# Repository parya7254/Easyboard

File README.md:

# Easyboard
A hot swappable tenkeyless (full size but without the number pad) mechanical keyboard with RGB lighting and an OLED (SSD1306) display! It will use a RP2040 Pro Micro as the controller, SK6812-MINI-E (reverse mount) LEDs for the backlight, and MX-style switches (and also MX-style hot swap sockets).

# Why did I Make This??
I really like designing my own things, like REALLY. And I also REALLY want a mechanical keyboard. So I thought to myself, *why not just make your own?* So I did one of my most complex projects ever, designing and building my own hot-swappable keyboard with RGB lights. And after about *more than* 60 **MIND GRUELING** hours of work, I managed to finally make a mechanical keyboard, one that was made by **me** and **me** only. And another reason for making this keyboard is that I have a lot of school work which requires a lot of typing and sometimes I write a lot of code, so this keyboard will help me work more efficiently.

# How did I Make This??
All of the PCB designing was done in KiCad and the case was designed in Fusion360. I started with a scematic and layed out my parts like so: 

And after that, I placed my parts on the PCB and then wired them:

The hardest part of designing this keyboard was wiring the things together in my PCB, expecially the LEDs. I ran into many rabbit holes during this process since lots of things were in the way and there was not encough space to wire some things so I had to move some traces and sometimes entirely rewire some things just so I can wire other things. Designing the keyboard made me want to give up and scrap everything and start another project, but I still continued and managed to finish everything.

# BOM
These are the parts that I need to build and assemble my PCB:

| Name | Purpose | Quantity | Total Cost (USD) | Link | Distributor |
|---|---|---|---|---|---|
| SSD1306 OLED Display | This will be the display on my keyboard. I currently plan on having it display the mode of the right 9 extra switches. | 1 | 2.50 | https://www.aliexpress.us/item/3256805954920554.html?spm=a2g0o.productlist.main.1.acdaE2guE2guy6&algo_pvid=447a40fe-ce76-4550-b662-5327f82a75f7&algo_exp_id=447a40fe-ce76-4550-b662-5327f82a75f7-0&pdp_ext_f=%7B%22order%22%3A%2222914%22%2C%22eval%22%3A%221%22%2C%22fromPage%22%3A%22search%22%7D&pdp_npi=6%40dis%21USD%212.51%212.50%21%21%2117.24%2117.15%21%402101f70717749984566174141ee445%2112000035944225408%21sea%21US%21861143113%21X%211%210%21n_tag%3A-29919%3Bd%3A19af3db4%3Bm03_new_user%3A-29895&curPageLogUid=5KU5UVX5hVAo&utparam-url=scene%3Asearch%7Cquery_from%3A%7Cx_object_id%3A1005006141235306%7C_p_origin_prod%3A | AliExpress |
| MX Stabilizers | These will be the stabilizers for the longer keys on my keyboard. This will ensure that the longer keycaps properly press when not pressed from the middle. | 1 | 2.86 | https://www.aliexpress.us/item/3256807026554334.html?spm=a2g0o.productlist.main.1.698f24e6GPCOAO&algo_pvid=6986125a-1875-4abe-a369-b66edb9fdb96&algo_exp_id=6986125a-1875-4abe-a369-b66edb9fdb96-0&pdp_ext_f=%7B%22order%22%3A%2283%22%2C%22eval%22%3A%221%22%2C%22fromPage%22%3A%22search%22%7D&pdp_npi=6%40dis%21USD%212.86%212.86%21%21%2119.65%2119.65%21%402101e2b017749981124183121e3966%2112000039826435204%21sea%21US%21861143113%21X%211%210%21n_tag%3A-29919%3Bd%3A19af3db4%3Bm03_new_user%3A-29895&curPageLogUid=vXwvaFnDovX6&utparam-url=scene%3Asearch%7Cquery_from%3A%7Cx_object_id%3A1005007212869086%7C_p_origin_prod%3A | AliExpress |
| Blue MX Hotswap Sockets (110pcs) | This will be to sockets which I solder to the PCB and where I insert my keyboard's switches. | 1 | 12.99 | https://www.amazon.com/DUROCK-Mechanical-Keyboard-Switches-Hot-Swap/dp/B0B4W8WFGS/ref=sr_1_7?crid=3PNPV81A8PUH7&dib=eyJ2IjoiMSJ9.JKoXkJJJrIVA4JnSSkGnSnjGCC1c4hQes6g1zrF8pFvOIEmMfUgJ5pp02OFyf2JeWhCTJmnAN4q3G-LvLOuBql6VJTJnxRGewD6-XjfYxSGo6HtCUGx8yAxFKqo13-YgVgIDzEERzdctNqCARGlgTNMMWP0Cxdv0wlmfE63BKVlXHsFmkzjJEkMkOGy9lDu44t9_Vt13ecWd9WDIXfqE_Q.RRCHw5LNrbPmqY88z8aOQsue-Tfpf6xlrtRnIY_J_gQ&dib_tag=se&keywords=hotswap%2Bsockets%2Bmx&qid=1774997653&sprefix=hotswap%2Bsocket%2Caps%2C140&sr=8-7&th=1 | Amazon |
| Keyboard PCB | This will be the main part of my keyboard! This is my circuit board with connects the components to the RP2040 Pro Micro. | 5 | 27.00 | https://cart.jlcpcb.com/quote?spm=jlcpcb.Public.2006 | JLCPCB |
| Green Frosted Translucent Clear Keycaps Set | These will be the keycaps for my keyboard! I chose the color green and also they are transparent so that the RGB lights shine though. | 1 | 16.99 | https://www.amazon.com/GUUKEY-Translucent-Shine-Through-Transparency-Mechanical/dp/B0FLK96YHS/ref=sr_1_3?crid=1ENZ1X3ES00VQ&dib=eyJ2IjoiMSJ9.I7pnMYchsMp-bVFs-8t_5AumUR2fDrr8YE76gmEcZGbXdxlwJu8_AAkgVcEPEsNVSN_SA7HxV4aJbe8cyMGeu89ntH00LOWfRLWGlidNYcLFfGzSm5UkZHD4eGqyAo5XHeqoyGSxBD-OXpWZBtiG16iisgaG0eoEzXPDPi6twUEGshXSF9cS__vJKIL8_iDx0pKE8X016OgZCxUxqKfG2d8N3Dy_bG0HyyhEg2jRx-Q.m5fVCbWabIUWUqADZR7fq_V4eNC2APTzMw1I3X1rxQQ&dib_tag=se&keywords=transparent%2Bgreen%2Bkeycaps%2Bmx&qid=1774990147&sprefix=transparent%2Bgreen%2Bkeycaps%2Bmx%2Caps%2C133&sr=8-3&th=1 | Amazon |
| SK6812 MINI-E (100pcs) | This will be the RGB LEDs of my keyboard! They are individually addressable as well (each led can have its own color) and they will add great aesthetics to my keyboard. | 1 | 3.49 | https://www.aliexpress.us/item/3256807677321116.html?spm=a2g0o.productlist.main.2.35d357e6bXG6Fa&algo_pvid=9bae5c18-19c7-4431-a748-378d3deebd81&algo_exp_id=9bae5c18-19c7-4431-a748-378d3deebd81-1&pdp_ext_f=%7B%22order%22%3A%22531%22%2C%22eval%22%3A%221%22%2C%22fromPage%22%3A%22search%22%7D&pdp_npi=6%40dis%21USD%213.49%213.49%21%21%213.49%213.49%21%402101d6fe17749205864375340ec439%2112000042594617264%21sea%21US%21861143113%21X%211%210%21n_tag%3A-29919%3Bd%3A19af3db4%3Bm03_new_user%3A-29895&curPageLogUid=H9eLn4OdO0JY&utparam-url=scene%3Asearch%7Cquery_from%3A%7Cx_object_id%3A1005007863635868%7C_p_origin_prod%3A | AliExpress |
| RP2040 Pro Micro | This is my keyboard's microcontroller. It will read the key presses from the key matrix and then convert them into key presses and then send keyboard commands to the connected device and it also will control the RGB lighting and the OLED display.. It is basically the ""brain"" of my keyboard. | 1 | 3.82 | https://www.aliexpress.us/item/3256806781060135.html?spm=a2g0o.productlist.main.1.75d062b2eSWZgQ&algo_pvid=1db491c0-3181-4dad-b148-b2b95c9bb695&algo_exp_id=1db491c0-3181-4dad-b148-b2b95c9bb695-0&pdp_ext_f=%7B%22order%22%3A%227169%22%2C%22eval%22%3A%221%22%2C%22orig_sl_item_id%22%3A%221005006967374887%22%2C%22orig_item_id%22%3A%221005009890367599%22%2C%22fromPage%22%3A%22search%22%7D&pdp_npi=6%40dis%21USD%216.48%213.11%21%21%2144.66%2121.44%21%402101df0e17749198865717046e5ea2%2112000038886039687%21sea%21US%21861143113%21XZ%211%210%21n_tag%3A-29919%3Bd%3A19af3db4%3Bm03_new_user%3A-29895&curPageLogUid=SrAHQR9XW5yz&utparam-url=scene%3Asearch%7Cquery_from%3A%7Cx_object_id%3A1005006967374887%7C_p_origin_prod%3A1005009890367599 | AliExpress |
| EPOMAKER Shadow Black Switches (100pcs) | These are the switches which will be used for my keyboard! | 1 | 19.99 | https://www.amazon.com/EPOMAKER-Mechanical-Switches-Keyboard-Pre-Lubed/dp/B0FYDQZ8HB/ref=sr_1_11?crid=1U34LH1S6O4TT&dib=eyJ2IjoiMSJ9.sZD0w0fIzMUCaV5YG3puFGZtG6dwW4pUS_EZhR3f8hiDH3pp0GB4T2VaDawQc9IybRuM4PJDiF0WhQhyN6jvBzeUSHCTjH3YTej49KHc8NuGcii3WUYmKEu9XZ83Us3_Xm0L7yCCNyTN1sGkM6aCd1uegF4RXI-MPjx5nbcpCevXdNGoZcz4q2Wl7Gohq1Nfs3aY56FeV-rw70tCRazUEOPahTbWXUitNsm_dx2fmo4.vV0_W4ZE6EAypwP-uPtM1gzeZPcmb4dmKXFzgEeno0A&dib_tag=se&keywords=100%2Bkeyboard%2Bswitch&qid=1775004672&sprefix=100%2Bkeyboard%2Bswitch%2Caps%2C169&sr=8-11&th=1 | Amazon |

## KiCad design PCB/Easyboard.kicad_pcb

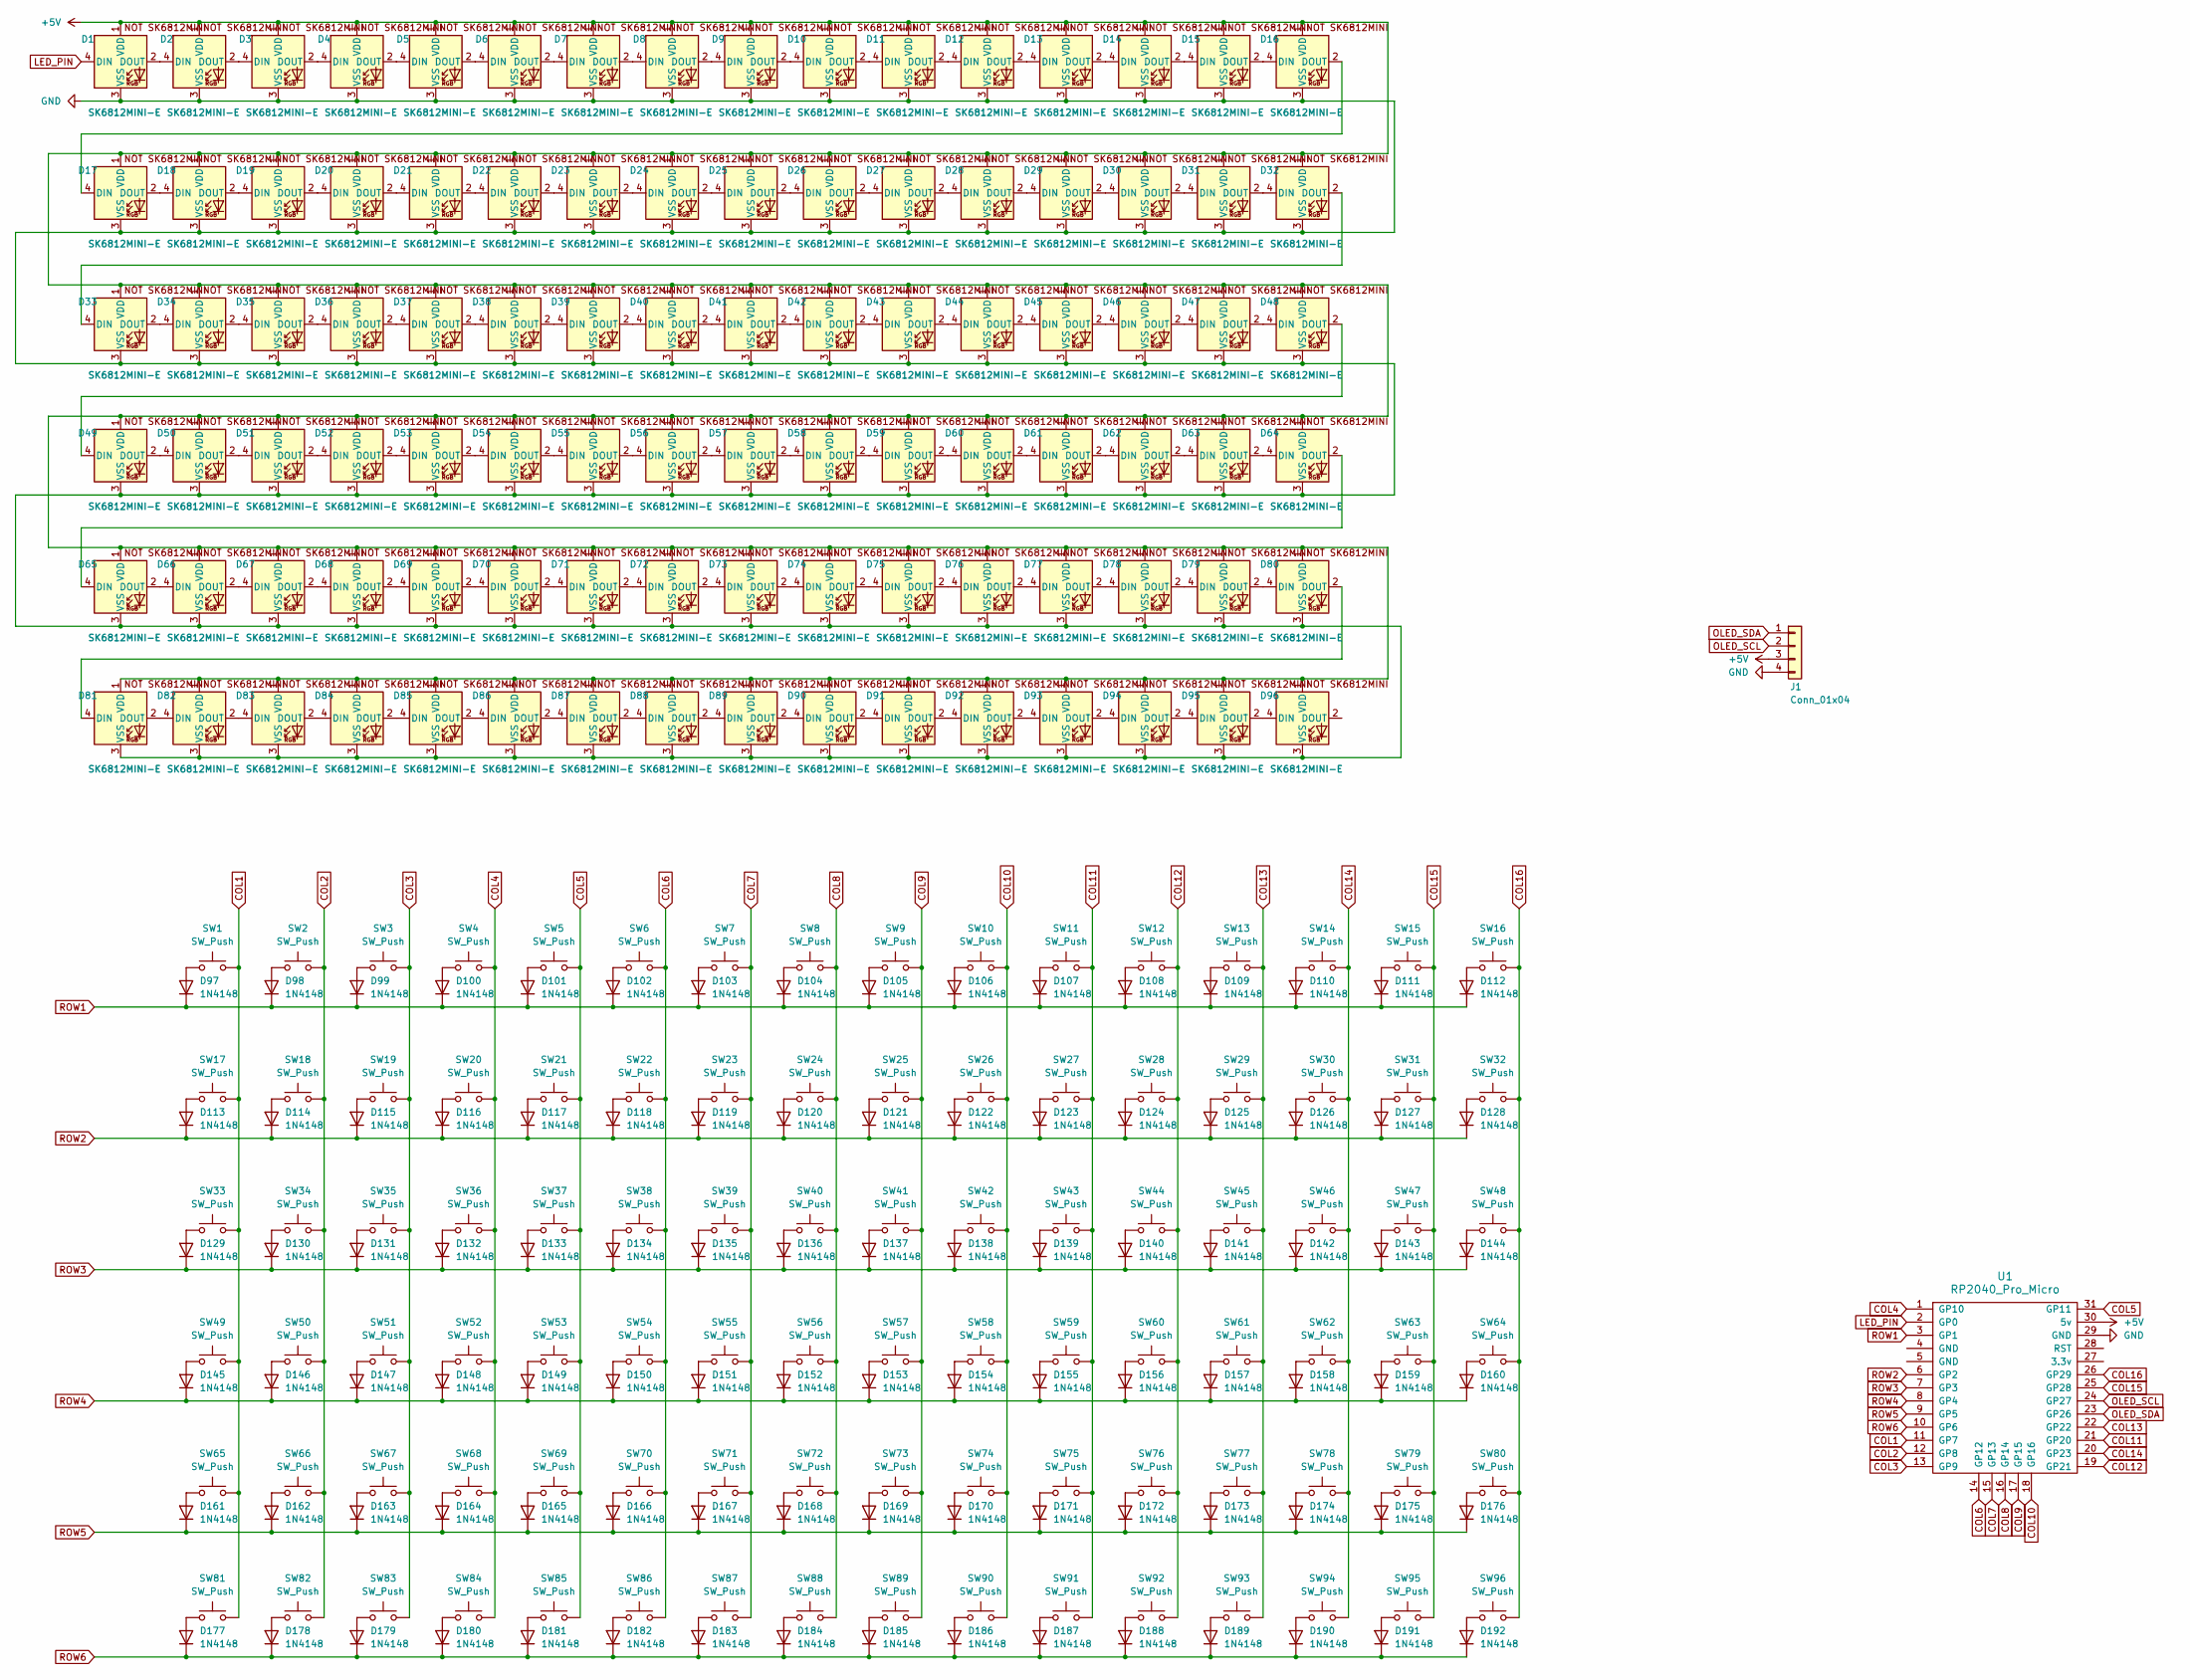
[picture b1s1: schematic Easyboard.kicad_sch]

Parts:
D1, D2, D3, D4, D5, D6, D7, D8, D9, D10, D11, D12, D13, D14, D15, D16, D17, D18, D19, D20, D21, D22, D23, D24, D25, D26, D27, D28, D29, D30, D31, D32, D33, D34, D35, D36, D37, D38, D39, D40, D41, D42, D43, D44, D45, D46, D47, D48, D49, D50, D51, D52, D53, D54, D55, D56, D57, D58, D59, D60, D61, D62, D63, D64, D65, D66, D67, D68, D69, D70, D71, D72, D73, D74, D75, D76, D77, D78, D79, D80, D81, D82, D83, D84, D85, D86, D87, D88, D89, D90, D91, D92, D93, D94, D95, D96: SK6812MINI-E; MX_SK6812MINI-E_REV
D97, D98, D99, D100, D101, D102, D103, D104, D105, D106, D107, D108, D109, D110, D111, D112, D113, D114, D115, D116, D117, D118, D119, D120, D121, D122, D123, D124, D125, D126, D127, D128, D129, D130, D131, D132, D133, D134, D135, D136, D137, D138, D139, D140, D141, D142, D143, D144, D145, D146, D147, D148, D149, D150, D151, D152, D153, D154, D155, D156, D157, D158, D159, D160, D161, D162, D163, D164, D165, D166, D167, D168, D169, D170, D171, D172, D173, D174, D175, D176, D177, D178, D179, D180, D181, D182, D183, D184, D185, D186, D187, D188, D189, D190, D191, D192: 1N4148; D_DO-35_SOD27_P7.62mm_Horizontal
J1: Conn_01x04; PinHeader_1x04_P2.54mm_Vertical
SW1, SW2, SW3, SW4, SW5, SW6, SW7, SW8, SW9, SW10, SW11, SW12, SW13, SW14, SW15, SW16, SW17, SW18, SW19, SW20, SW21, SW22, SW23, SW24, SW25, SW26, SW27, SW28, SW29, SW31, SW32, SW33, SW35, SW36, SW37, SW38, SW39, SW40, SW41, SW42, SW43, SW44, SW45, SW46, SW48, SW49, SW50, SW52, SW53, SW54, SW55, SW56, SW57, SW58, SW59, SW60, SW61, SW62, SW65, SW66, SW67, SW68, SW69, SW70, SW71, SW72, SW73, SW74, SW76, SW85, SW86, SW87, SW88, SW89, SW90, SW91, SW92, SW93, SW94, SW95, SW96: SW_Push; Hotswap_MX_1.00u
SW30: SW_Push; Hotswap_MX_2.00u
SW34, SW47: SW_Push; Hotswap_MX_1.50u
SW51: SW_Push; Hotswap_MX_1.75u
SW63, SW64: SW_Push; Hotswap_MX_2.25u
SW75: SW_Push; Hotswap_MX_2.75u
SW77, SW78, SW79, SW81, SW82, SW83, SW84: SW_Push; Hotswap_MX_1.25u
SW80: SW_Push; Hotswap_MX_6.25u
U1: RP2040_Pro_Micro

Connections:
+5V: D1.1 (VDD), D2.1 (VDD), D3.1 (VDD), D4.1 (VDD), D5.1 (VDD), D6.1 (VDD), D7.1 (VDD), D8.1 (VDD), D9.1 (VDD), D10.1 (VDD), D11.1 (VDD), D12.1 (VDD), D13.1 (VDD), D14.1 (VDD), D15.1 (VDD), D16.1 (VDD), D17.1 (VDD), D18.1 (VDD), D19.1 (VDD), D20.1 (VDD), D21.1 (VDD), D22.1 (VDD), D23.1 (VDD), D24.1 (VDD), D25.1 (VDD), D26.1 (VDD), D27.1 (VDD), D28.1 (VDD), D29.1 (VDD), D30.1 (VDD), D31.1 (VDD), D32.1 (VDD), D33.1 (VDD), D34.1 (VDD), D35.1 (VDD), D36.1 (VDD), D37.1 (VDD), D38.1 (VDD), D39.1 (VDD), D40.1 (VDD), D41.1 (VDD), D42.1 (VDD), D43.1 (VDD), D44.1 (VDD), D45.1 (VDD), D46.1 (VDD), D47.1 (VDD), D48.1 (VDD), D49.1 (VDD), D50.1 (VDD), D51.1 (VDD), D52.1 (VDD), D53.1 (VDD), D54.1 (VDD), D55.1 (VDD), D56.1 (VDD), D57.1 (VDD), D58.1 (VDD), D59.1 (VDD), D60.1 (VDD), D61.1 (VDD), D62.1 (VDD), D63.1 (VDD), D64.1 (VDD), D65.1 (VDD), D66.1 (VDD), D67.1 (VDD), D68.1 (VDD), D69.1 (VDD), D70.1 (VDD), D71.1 (VDD), D72.1 (VDD), D73.1 (VDD), D74.1 (VDD), D75.1 (VDD), D76.1 (VDD), D77.1 (VDD), D78.1 (VDD), D79.1 (VDD), D80.1 (VDD), D81.1 (VDD), D82.1 (VDD), D83.1 (VDD), D84.1 (VDD), D85.1 (VDD), D86.1 (VDD), D87.1 (VDD), D88.1 (VDD), D89.1 (VDD), D90.1 (VDD), D91.1 (VDD), D92.1 (VDD), D93.1 (VDD), D94.1 (VDD), D95.1 (VDD), D96.1 (VDD), J1.3, U1.30 (5v)
COL1: SW1.2, SW17.2, SW33.2, SW49.2, SW65.2, SW81.2, U1.11 (GP7)
COL2: SW2.2, SW18.2, SW34.2, SW50.2, SW66.2, SW82.2, U1.12 (GP8)
COL3: SW3.2, SW19.2, SW35.2, SW51.2, SW67.2, SW83.2, U1.13 (GP9)
COL4: SW4.2, SW20.2, SW36.2, SW52.2, SW68.2, SW84.2, U1.1 (GP10)
COL5: SW5.2, SW21.2, SW37.2, SW53.2, SW69.2, SW85.2, U1.31 (GP11)
COL6: SW6.2, SW22.2, SW38.2, SW54.2, SW70.2, SW86.2, U1.14 (GP12)
COL7: SW7.2, SW23.2, SW39.2, SW55.2, SW71.2, SW87.2, U1.15 (GP13)
COL8: SW8.2, SW24.2, SW40.2, SW56.2, SW72.2, SW88.2, U1.16 (GP14)
COL9: SW9.2, SW25.2, SW41.2, SW57.2, SW73.2, SW89.2, U1.17 (GP15)
COL10: SW10.2, SW26.2, SW42.2, SW58.2, SW74.2, SW90.2, U1.18 (GP16)
COL11: SW11.2, SW27.2, SW43.2, SW59.2, SW75.2, SW91.2, U1.21 (GP20)
COL12: SW12.2, SW28.2, SW44.2, SW60.2, SW76.2, SW92.2, U1.19 (GP21)
COL13: SW13.2, SW29.2, SW45.2, SW61.2, SW77.2, SW93.2, U1.22 (GP22)
COL14: SW14.2, SW30.2, SW46.2, SW62.2, SW78.2, SW94.2, U1.20 (GP23)
COL15: SW15.2, SW31.2, SW47.2, SW63.2, SW79.2, SW95.2, U1.25 (GP28)
COL16: SW16.2, SW32.2, SW48.2, SW64.2, SW80.2, SW96.2, U1.26 (GP29)
GND: D1.3 (VSS), D2.3 (VSS), D3.3 (VSS), D4.3 (VSS), D5.3 (VSS), D6.3 (VSS), D7.3 (VSS), D8.3 (VSS), D9.3 (VSS), D10.3 (VSS), D11.3 (VSS), D12.3 (VSS), D13.3 (VSS), D14.3 (VSS), D15.3 (VSS), D16.3 (VSS), D17.3 (VSS), D18.3 (VSS), D19.3 (VSS), D20.3 (VSS), D21.3 (VSS), D22.3 (VSS), D23.3 (VSS), D24.3 (VSS), D25.3 (VSS), D26.3 (VSS), D27.3 (VSS), D28.3 (VSS), D29.3 (VSS), D30.3 (VSS), D31.3 (VSS), D32.3 (VSS), D33.3 (VSS), D34.3 (VSS), D35.3 (VSS), D36.3 (VSS), D37.3 (VSS), D38.3 (VSS), D39.3 (VSS), D40.3 (VSS), D41.3 (VSS), D42.3 (VSS), D43.3 (VSS), D44.3 (VSS), D45.3 (VSS), D46.3 (VSS), D47.3 (VSS), D48.3 (VSS), D49.3 (VSS), D50.3 (VSS), D51.3 (VSS), D52.3 (VSS), D53.3 (VSS), D54.3 (VSS), D55.3 (VSS), D56.3 (VSS), D57.3 (VSS), D58.3 (VSS), D59.3 (VSS), D60.3 (VSS), D61.3 (VSS), D62.3 (VSS), D63.3 (VSS), D64.3 (VSS), D65.3 (VSS), D66.3 (VSS), D67.3 (VSS), D68.3 (VSS), D69.3 (VSS), D70.3 (VSS), D71.3 (VSS), D72.3 (VSS), D73.3 (VSS), D74.3 (VSS), D75.3 (VSS), D76.3 (VSS), D77.3 (VSS), D78.3 (VSS), D79.3 (VSS), D80.3 (VSS), D81.3 (VSS), D82.3 (VSS), D83.3 (VSS), D84.3 (VSS), D85.3 (VSS), D86.3 (VSS), D87.3 (VSS), D88.3 (VSS), D89.3 (VSS), D90.3 (VSS), D91.3 (VSS), D92.3 (VSS), D93.3 (VSS), D94.3 (VSS), D95.3 (VSS), D96.3 (VSS), J1.4, U1.29 (GND)
LED_PIN: D1.4 (DIN), U1.2 (GP0)
unnamed: D1.2 (DOUT), D2.4 (DIN)
unnamed: D2.2 (DOUT), D3.4 (DIN)
unnamed: D3.2 (DOUT), D4.4 (DIN)
unnamed: D4.2 (DOUT), D5.4 (DIN)
unnamed: D5.2 (DOUT), D6.4 (DIN)
unnamed: D6.2 (DOUT), D7.4 (DIN)
unnamed: D7.2 (DOUT), D8.4 (DIN)
unnamed: D8.2 (DOUT), D9.4 (DIN)
unnamed: D9.2 (DOUT), D10.4 (DIN)
unnamed: D10.2 (DOUT), D11.4 (DIN)
unnamed: D11.2 (DOUT), D12.4 (DIN)
unnamed: D12.2 (DOUT), D13.4 (DIN)
unnamed: D13.2 (DOUT), D14.4 (DIN)
unnamed: D14.2 (DOUT), D15.4 (DIN)
unnamed: D15.2 (DOUT), D16.4 (DIN)
unnamed: D16.2 (DOUT), D17.4 (DIN)
unnamed: D17.2 (DOUT), D18.4 (DIN)
unnamed: D18.2 (DOUT), D19.4 (DIN)
unnamed: D19.2 (DOUT), D20.4 (DIN)
unnamed: D20.2 (DOUT), D21.4 (DIN)
unnamed: D21.2 (DOUT), D22.4 (DIN)
unnamed: D22.2 (DOUT), D23.4 (DIN)
unnamed: D23.2 (DOUT), D24.4 (DIN)
unnamed: D24.2 (DOUT), D25.4 (DIN)
unnamed: D25.2 (DOUT), D26.4 (DIN)
unnamed: D26.2 (DOUT), D27.4 (DIN)
unnamed: D27.2 (DOUT), D28.4 (DIN)
unnamed: D28.2 (DOUT), D29.4 (DIN)
unnamed: D29.2 (DOUT), D30.4 (DIN)
unnamed: D30.2 (DOUT), D31.4 (DIN)
unnamed: D31.2 (DOUT), D32.4 (DIN)
unnamed: D32.2 (DOUT), D33.4 (DIN)
unnamed: D33.2 (DOUT), D34.4 (DIN)
unnamed: D34.2 (DOUT), D35.4 (DIN)
unnamed: D35.2 (DOUT), D36.4 (DIN)
unnamed: D36.2 (DOUT), D37.4 (DIN)
unnamed: D37.2 (DOUT), D38.4 (DIN)
unnamed: D38.2 (DOUT), D39.4 (DIN)
unnamed: D39.2 (DOUT), D40.4 (DIN)
unnamed: D40.2 (DOUT), D41.4 (DIN)
unnamed: D41.2 (DOUT), D42.4 (DIN)
unnamed: D42.2 (DOUT), D43.4 (DIN)
unnamed: D43.2 (DOUT), D44.4 (DIN)
unnamed: D44.2 (DOUT), D45.4 (DIN)
unnamed: D45.2 (DOUT), D46.4 (DIN)
unnamed: D46.2 (DOUT), D47.4 (DIN)
unnamed: D47.2 (DOUT), D48.4 (DIN)
unnamed: D48.2 (DOUT), D49.4 (DIN)
unnamed: D49.2 (DOUT), D50.4 (DIN)
unnamed: D50.2 (DOUT), D51.4 (DIN)
unnamed: D51.2 (DOUT), D52.4 (DIN)
unnamed: D52.2 (DOUT), D53.4 (DIN)
unnamed: D53.2 (DOUT), D54.4 (DIN)
unnamed: D54.2 (DOUT), D55.4 (DIN)
unnamed: D55.2 (DOUT), D56.4 (DIN)
unnamed: D56.2 (DOUT), D57.4 (DIN)
unnamed: D57.2 (DOUT), D58.4 (DIN)
unnamed: D58.2 (DOUT), D59.4 (DIN)
unnamed: D59.2 (DOUT), D60.4 (DIN)
unnamed: D60.2 (DOUT), D61.4 (DIN)
unnamed: D61.2 (DOUT), D62.4 (DIN)
unnamed: D62.2 (DOUT), D63.4 (DIN)
unnamed: D63.2 (DOUT), D64.4 (DIN)
unnamed: D64.2 (DOUT), D65.4 (DIN)
unnamed: D65.2 (DOUT), D66.4 (DIN)
unnamed: D66.2 (DOUT), D67.4 (DIN)
unnamed: D67.2 (DOUT), D68.4 (DIN)
unnamed: D68.2 (DOUT), D69.4 (DIN)
unnamed: D69.2 (DOUT), D70.4 (DIN)
unnamed: D70.2 (DOUT), D71.4 (DIN)
unnamed: D71.2 (DOUT), D72.4 (DIN)
unnamed: D72.2 (DOUT), D73.4 (DIN)
unnamed: D73.2 (DOUT), D74.4 (DIN)
unnamed: D74.2 (DOUT), D75.4 (DIN)
unnamed: D75.2 (DOUT), D76.4 (DIN)
unnamed: D76.2 (DOUT), D77.4 (DIN)
unnamed: D77.2 (DOUT), D78.4 (DIN)
unnamed: D78.2 (DOUT), D79.4 (DIN)
unnamed: D79.2 (DOUT), D80.4 (DIN)
unnamed: D80.2 (DOUT), D81.4 (DIN)
unnamed: D81.2 (DOUT), D82.4 (DIN)
unnamed: D82.2 (DOUT), D83.4 (DIN)
unnamed: D83.2 (DOUT), D84.4 (DIN)
unnamed: D84.2 (DOUT), D85.4 (DIN)
unnamed: D85.2 (DOUT), D86.4 (DIN)
unnamed: D86.2 (DOUT), D87.4 (DIN)
unnamed: D87.2 (DOUT), D88.4 (DIN)
unnamed: D88.2 (DOUT), D89.4 (DIN)
unnamed: D89.2 (DOUT), D90.4 (DIN)
unnamed: D90.2 (DOUT), D91.4 (DIN)
unnamed: D91.2 (DOUT), D92.4 (DIN)
unnamed: D92.2 (DOUT), D93.4 (DIN)
unnamed: D93.2 (DOUT), D94.4 (DIN)
unnamed: D94.2 (DOUT), D95.4 (DIN)
unnamed: D95.2 (DOUT), D96.4 (DIN)
unnamed: D97.2 (A), SW1.1
unnamed: D98.2 (A), SW2.1
unnamed: D99.2 (A), SW3.1
unnamed: D100.2 (A), SW4.1
unnamed: D101.2 (A), SW5.1
unnamed: D102.2 (A), SW6.1
unnamed: D103.2 (A), SW7.1
unnamed: D104.2 (A), SW8.1
unnamed: D105.2 (A), SW9.1
unnamed: D106.2 (A), SW10.1
unnamed: D107.2 (A), SW11.1
unnamed: D108.2 (A), SW12.1
unnamed: D109.2 (A), SW13.1
unnamed: D110.2 (A), SW14.1
unnamed: D111.2 (A), SW15.1
unnamed: D112.2 (A), SW16.1
unnamed: D113.2 (A), SW17.1
unnamed: D114.2 (A), SW18.1
unnamed: D115.2 (A), SW19.1
unnamed: D116.2 (A), SW20.1
unnamed: D117.2 (A), SW21.1
unnamed: D118.2 (A), SW22.1
unnamed: D119.2 (A), SW23.1
unnamed: D120.2 (A), SW24.1
unnamed: D121.2 (A), SW25.1
unnamed: D122.2 (A), SW26.1
unnamed: D123.2 (A), SW27.1
unnamed: D124.2 (A), SW28.1
unnamed: D125.2 (A), SW29.1
unnamed: D126.2 (A), SW30.1
unnamed: D127.2 (A), SW31.1
unnamed: D128.2 (A), SW32.1
unnamed: D129.2 (A), SW33.1
unnamed: D130.2 (A), SW34.1
unnamed: D131.2 (A), SW35.1
unnamed: D132.2 (A), SW36.1
unnamed: D133.2 (A), SW37.1
unnamed: D134.2 (A), SW38.1
unnamed: D135.2 (A), SW39.1
unnamed: D136.2 (A), SW40.1
unnamed: D137.2 (A), SW41.1
unnamed: D138.2 (A), SW42.1
unnamed: D139.2 (A), SW43.1
unnamed: D140.2 (A), SW44.1
unnamed: D141.2 (A), SW45.1
unnamed: D142.2 (A), SW46.1
unnamed: D143.2 (A), SW47.1
unnamed: D144.2 (A), SW48.1
unnamed: D145.2 (A), SW49.1
unnamed: D146.2 (A), SW50.1
unnamed: D147.2 (A), SW51.1
unnamed: D148.2 (A), SW52.1
unnamed: D149.2 (A), SW53.1
unnamed: D150.2 (A), SW54.1
unnamed: D151.2 (A), SW55.1
unnamed: D152.2 (A), SW56.1
unnamed: D153.2 (A), SW57.1
unnamed: D154.2 (A), SW58.1
unnamed: D155.2 (A), SW59.1
unnamed: D156.2 (A), SW60.1
unnamed: D157.2 (A), SW61.1
unnamed: D158.2 (A), SW62.1
unnamed: D159.2 (A), SW63.1
unnamed: D160.2 (A), SW64.1
unnamed: D161.2 (A), SW65.1
unnamed: D162.2 (A), SW66.1
unnamed: D163.2 (A), SW67.1
unnamed: D164.2 (A), SW68.1
unnamed: D165.2 (A), SW69.1
unnamed: D166.2 (A), SW70.1
unnamed: D167.2 (A), SW71.1
unnamed: D168.2 (A), SW72.1
unnamed: D169.2 (A), SW73.1
unnamed: D170.2 (A), SW74.1
unnamed: D171.2 (A), SW75.1
unnamed: D172.2 (A), SW76.1
unnamed: D173.2 (A), SW77.1
unnamed: D174.2 (A), SW78.1
unnamed: D175.2 (A), SW79.1
unnamed: D176.2 (A), SW80.1
unnamed: D177.2 (A), SW81.1
unnamed: D178.2 (A), SW82.1
unnamed: D179.2 (A), SW83.1
unnamed: D180.2 (A), SW84.1
unnamed: D181.2 (A), SW85.1
unnamed: D182.2 (A), SW86.1
unnamed: D183.2 (A), SW87.1
unnamed: D184.2 (A), SW88.1
unnamed: D185.2 (A), SW89.1
unnamed: D186.2 (A), SW90.1
unnamed: D187.2 (A), SW91.1
unnamed: D188.2 (A), SW92.1
unnamed: D189.2 (A), SW93.1
unnamed: D190.2 (A), SW94.1
unnamed: D191.2 (A), SW95.1
unnamed: D192.2 (A), SW96.1
OLED_SCL: J1.2, U1.24 (GP27)
OLED_SDA: J1.1, U1.23 (GP26)
ROW1: D97.1 (K), D98.1 (K), D99.1 (K), D100.1 (K), D101.1 (K), D102.1 (K), D103.1 (K), D104.1 (K), D105.1 (K), D106.1 (K), D107.1 (K), D108.1 (K), D109.1 (K), D110.1 (K), D111.1 (K), D112.1 (K), U1.3 (GP1)
ROW2: D113.1 (K), D114.1 (K), D115.1 (K), D116.1 (K), D117.1 (K), D118.1 (K), D119.1 (K), D120.1 (K), D121.1 (K), D122.1 (K), D123.1 (K), D124.1 (K), D125.1 (K), D126.1 (K), D127.1 (K), D128.1 (K), U1.6 (GP2)
ROW3: D129.1 (K), D130.1 (K), D131.1 (K), D132.1 (K), D133.1 (K), D134.1 (K), D135.1 (K), D136.1 (K), D137.1 (K), D138.1 (K), D139.1 (K), D140.1 (K), D141.1 (K), D142.1 (K), D143.1 (K), D144.1 (K), U1.7 (GP3)
ROW4: D145.1 (K), D146.1 (K), D147.1 (K), D148.1 (K), D149.1 (K), D150.1 (K), D151.1 (K), D152.1 (K), D153.1 (K), D154.1 (K), D155.1 (K), D156.1 (K), D157.1 (K), D158.1 (K), D159.1 (K), D160.1 (K), U1.8 (GP4)
ROW5: D161.1 (K), D162.1 (K), D163.1 (K), D164.1 (K), D165.1 (K), D166.1 (K), D167.1 (K), D168.1 (K), D169.1 (K), D170.1 (K), D171.1 (K), D172.1 (K), D173.1 (K), D174.1 (K), D175.1 (K), D176.1 (K), U1.9 (GP5)
ROW6: D177.1 (K), D178.1 (K), D179.1 (K), D180.1 (K), D181.1 (K), D182.1 (K), D183.1 (K), D184.1 (K), D185.1 (K), D186.1 (K), D187.1 (K), D188.1 (K), D189.1 (K), D190.1 (K), D191.1 (K), D192.1 (K), U1.10 (GP6)

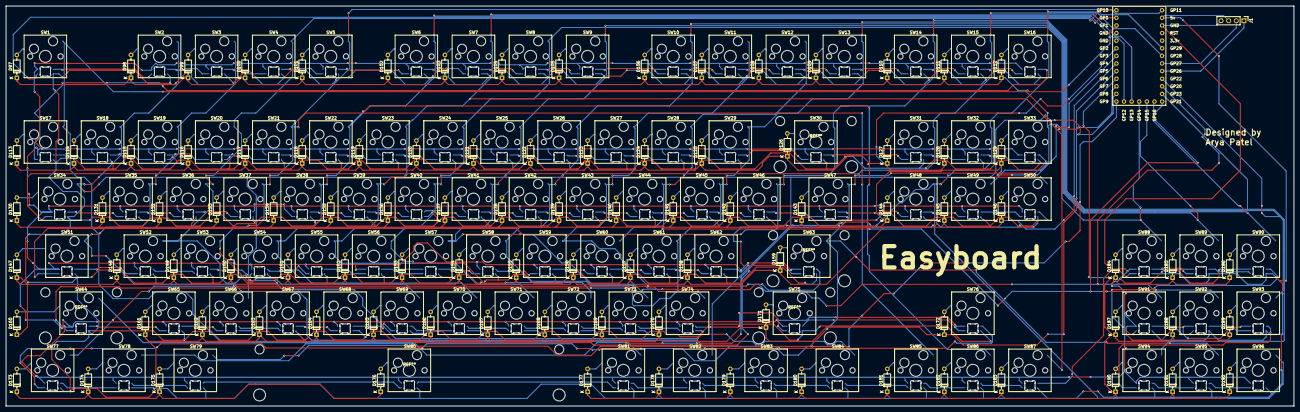
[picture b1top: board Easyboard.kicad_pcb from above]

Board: 2 copper layers, 429.8 x 133.5 mm, 290 parts (0 on the bottom side), 218 nets.

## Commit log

2026-04-04 Finished Code!!
2026-04-06 Create placeholder
2026-04-06 Uploaded Files
2026-04-06 Enhance README with project details and BOM
    Added detailed project description, including the rationale for creating the keyboard, design process, and a bill of materials (BOM) with links to components.
2026-04-08 Rename Easyboard.zip to Easyboard-Gerber.zip
2026-04-08 Added Seperate Top and Bottom Case Files
